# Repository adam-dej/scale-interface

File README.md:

scale-interface
===============

A simple USART / Bluetooth interface for a kitchen scale

http://adam-dej.github.io/2014/07/08/scale-interface.html

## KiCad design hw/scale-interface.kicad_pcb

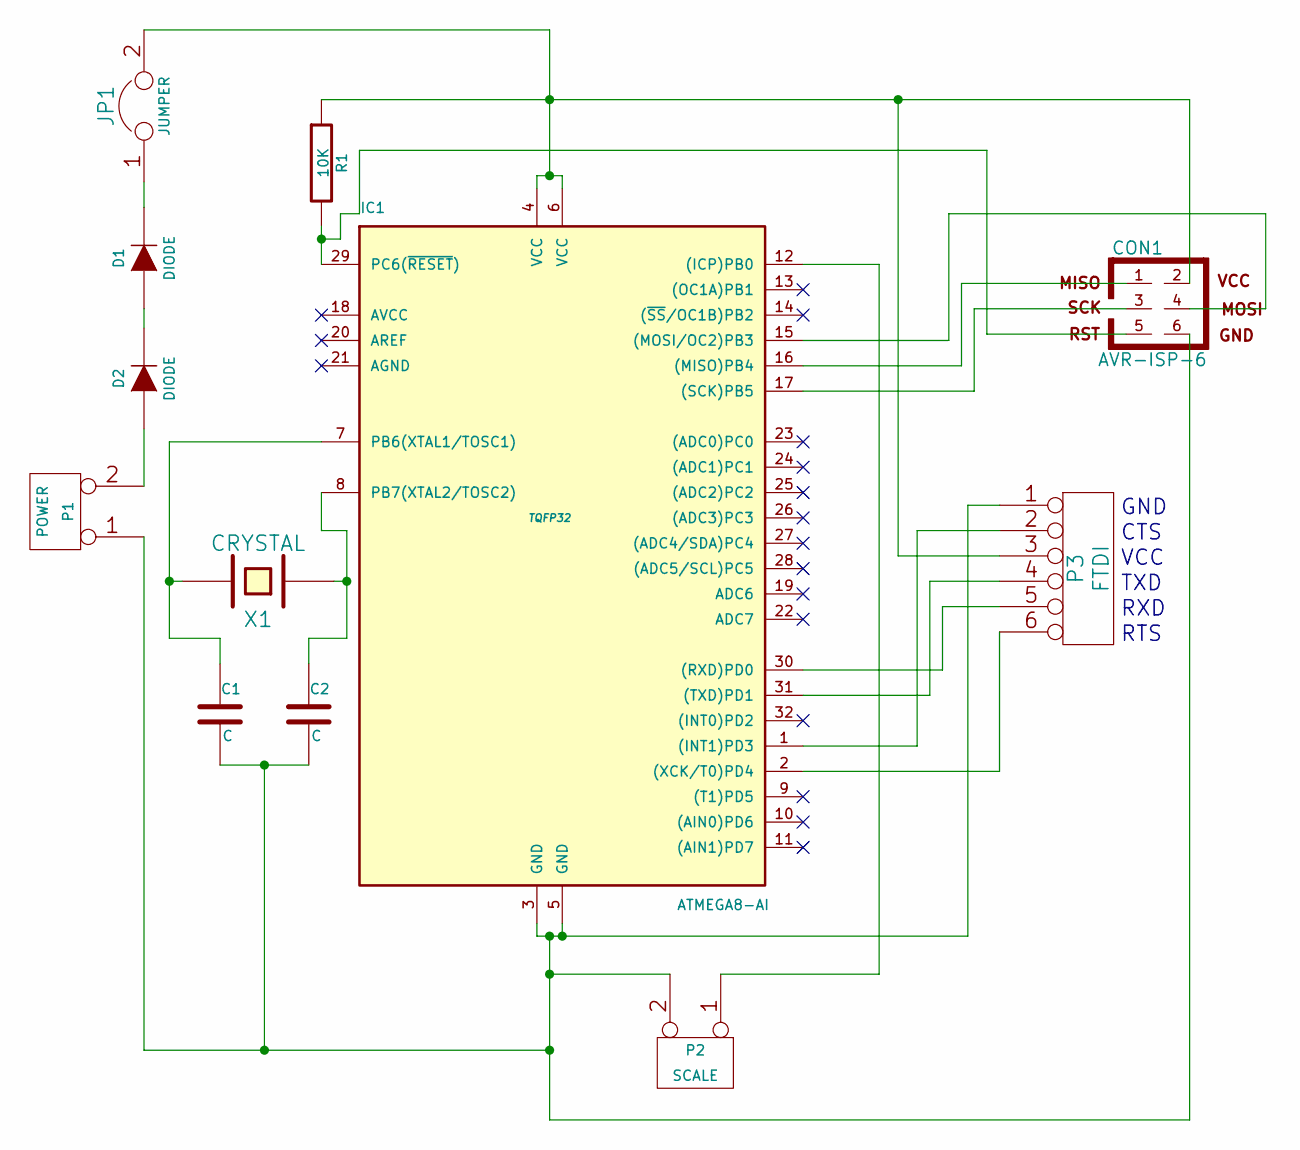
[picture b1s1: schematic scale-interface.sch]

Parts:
C1, C2: C
CON1: AVR-ISP-6
D1, D2: DIODE
IC1: ATMEGA8-AI; TQFP32
JP1: JUMPER
P1: POWER
P2: SCALE
P3: FTDI
R1: 10K
X1: CRYSTAL

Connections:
unnamed: CON1.4, IC1.15 ((MOSI/OC2)PB3)
unnamed: CON1.1, IC1.16 ((MISO)PB4)
unnamed: CON1.3, IC1.17 ((SCK)PB5)
unnamed: CON1.5, IC1.29 (PC6(~RESET~)), R1.2
unnamed: C1.2, C2.2, CON1.6, IC1.3 (GND), IC1.5 (GND), P1.1, P2.2 (PM), P3.1
unnamed: D2.1 (A), P1.2 (PM)
unnamed: D1.1 (A), D2.2 (K)
unnamed: D1.2 (K), JP1.1
unnamed: IC1.12 ((ICP)PB0), P2.1
unnamed: IC1.1 ((INT1)PD3), P3.2
unnamed: IC1.31 ((TXD)PD1), P3.4
unnamed: IC1.30 ((RXD)PD0), P3.5
unnamed: IC1.2 ((XCK/T0)PD4), P3.6
unnamed: CON1.2, IC1.4 (VCC), IC1.6 (VCC), JP1.2, P3.3, R1.1
unnamed: C2.1, IC1.8 (PB7(XTAL2/TOSC2)), X1.1
unnamed: C1.1, IC1.7 (PB6(XTAL1/TOSC1)), X1.2

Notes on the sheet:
GND
CTS
VCC
TXD
RXD
RTS

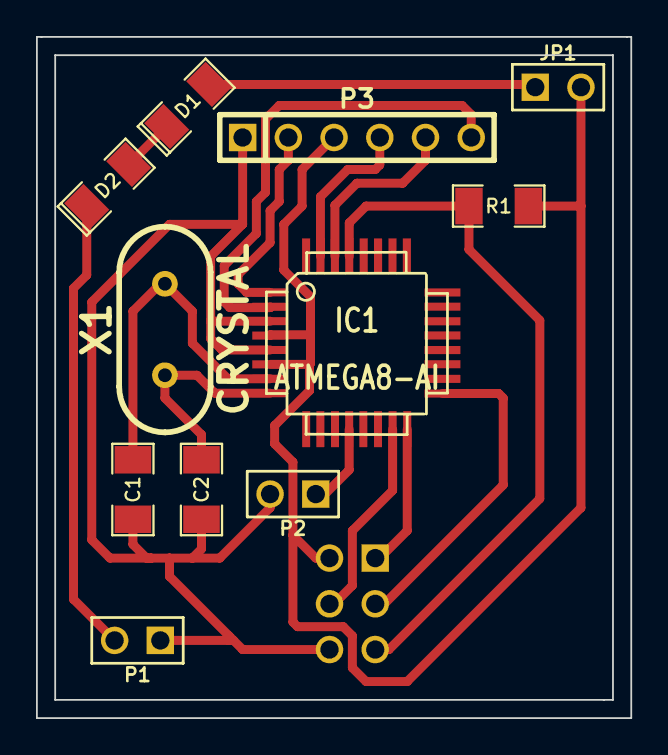
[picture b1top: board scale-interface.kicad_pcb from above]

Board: 2 copper layers, 33.0 x 37.8 mm, 12 parts (1 on the bottom side), 16 nets.

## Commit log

2014-07-06 Add .gitignore for HW section
2014-07-06 Add schematics and PCB layout
2014-07-06 Add gitignore for SW part
2014-07-06 Add Makefile
2014-07-08 Firmware import
2014-07-09 Align comments properly
